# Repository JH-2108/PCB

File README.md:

# Small devboard 

A custom RP2040-based development board designed from scratch in KiCAD as part of Hack Club Half Life. 

The DevBoard is a compact general-purpose development platform with native USB-C connectivity, external QSPI flash, 3.3V power regulation, GPIO breakout, onboard controls, and a status LED. The board is intended to be used for embedded programming, electronics experimentation, robotics, sensors, displays, and future hardware projects. 

# Features 
- Raspberry Pi RP2040 microcontroller
- Native USB-C connectivity
- External QSPI flash
- 12 MHz crystal oscillator
- 3.3V power regulation
- 2x20 GPIO breakout pins
- BOOTSEL and RESET buttons
- Onboard status LED
- SMD components
- Custom PCB designed in KiCAD

# Hardware 
The board is built around the RP2040 and follows the required circuity for its power, clock, USB, and external flash interfaces. 

# Main components
- RP2040 MCU
- W25Q128 QSPI flash
- 12 MHz crystal
- USB-C connector
- 3.3V LDO regulator
- Decoupling and filtering capacitors
- USB-C CC resistors
- GPIO headers
- RESET and BOOTSEL buttons
- Status LED

# Firmware
The devboard will be programmed using the Raspberry Pi Pico SDK and C/C++. 

The initial firmware will provide: 
- RP2040 boot and initialization
- USB connectivity
- GPIO testing
- Status LED control
- Board diagnostics
- USB serial communication

A diagnostic firmware can be used to verify that the assembled PCB is functioning correctly. 

# PC software
A small optional Python utility may be developed to communicated with the board over USB serial. 

This can be used to 
- Display board information
- Run hardware tests
- Control the onboard LED
- Test GPIO
- Monitor diagnostic output

# Design
The PCB and schematic are designed using KiCAD. 
Project files include: 
- Schematic
- PCB layout
- Component/footprint assignments
- BOM
- Manufacturing files

# Design process
1. select and verify components for pricing and whether it is within budget range
2. create the schematic
3. assign symbols and footprints
4. design the PCB layout
5. route the board
6. run electrical and design rule checks
7. generate gerber files
8. assemble the PCB
9. develop and test firmware
10. test the complete board

# Project goals
The main goal is to design and build a fully functioning custom development board rather than relying on an existing development board such as the Raspberry Pi Pico. 

The project combines: 
- PCB design
- embedded systems
- electronics
- Firmware development
- USB communication
- hardware testing
- software development

# project images

**Schematic** 

**PCB layout**

**3d Render**

**Finished PCB**
a photo will be added here

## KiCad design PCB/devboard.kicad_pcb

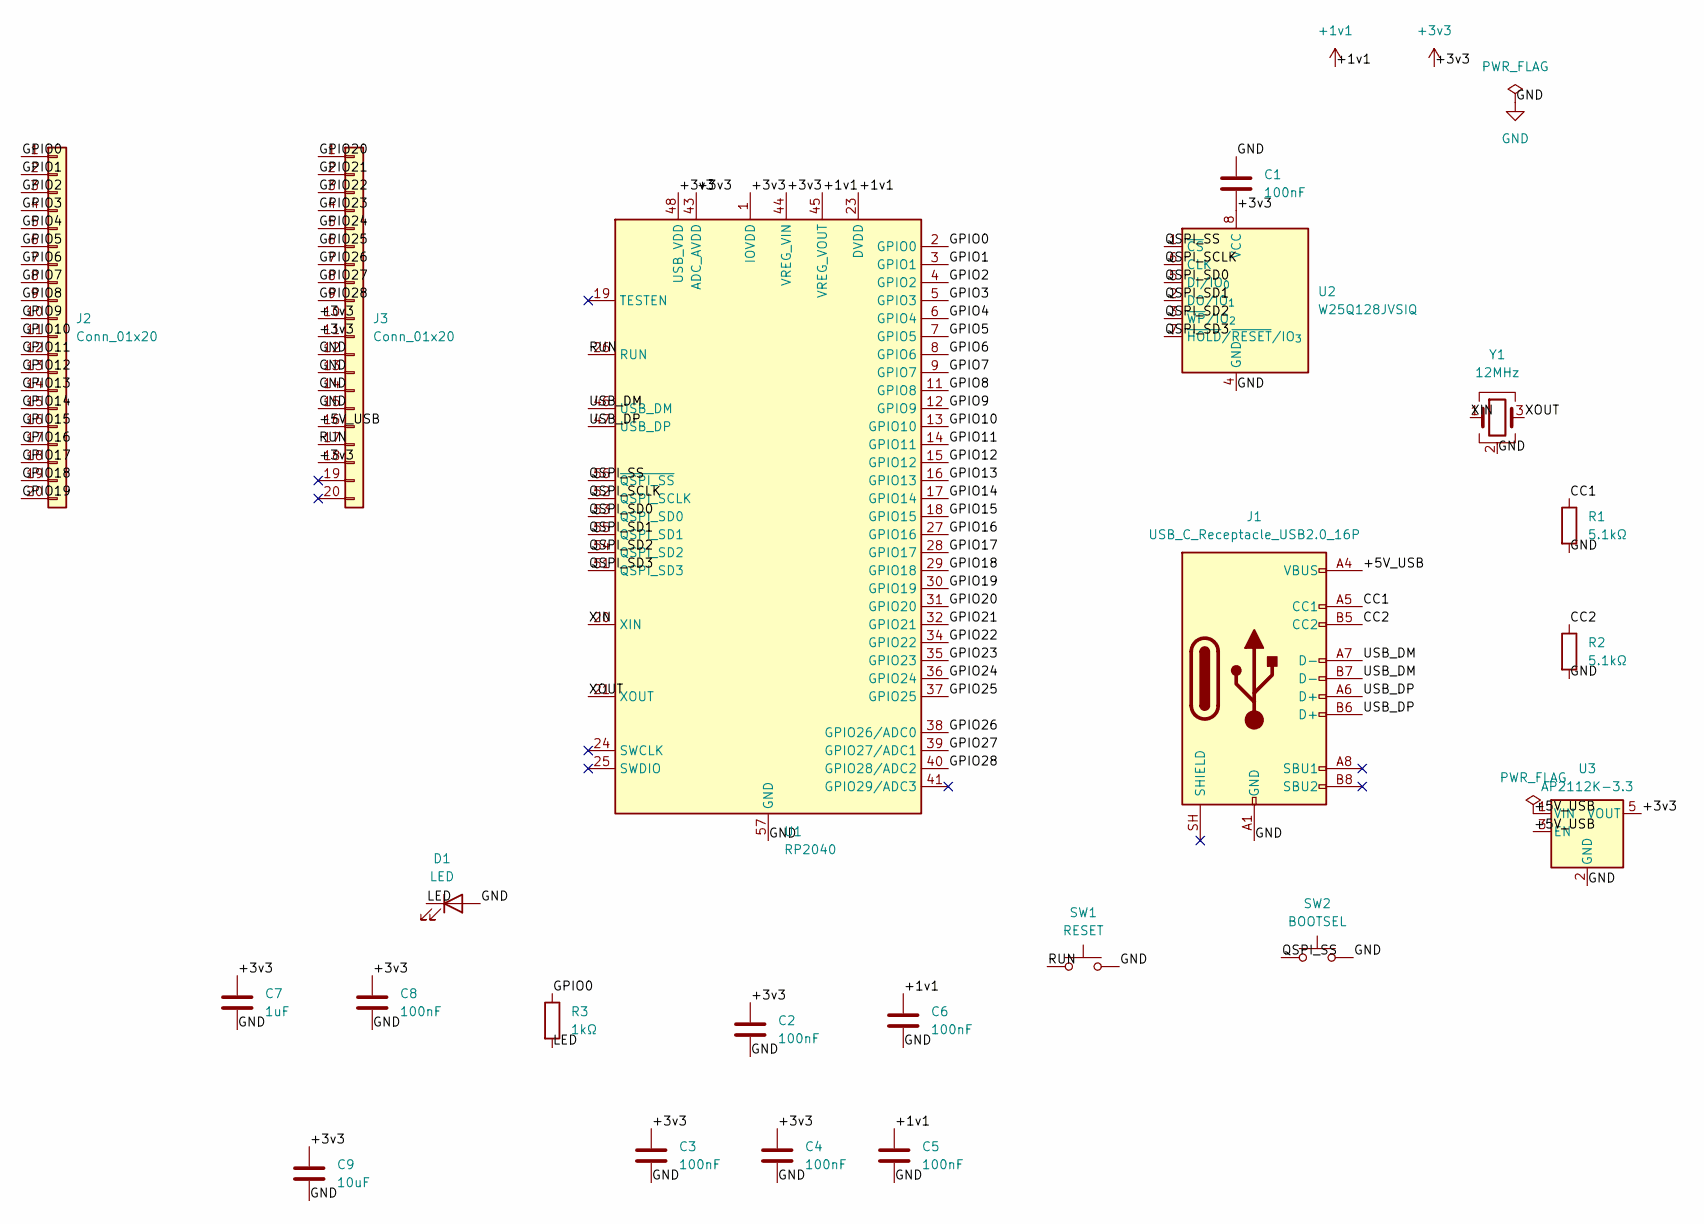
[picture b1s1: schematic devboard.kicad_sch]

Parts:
C1, C2, C3, C4, C5, C6, C8: 100nF; C_0603_1608Metric
C7: 1uF; C_0603_1608Metric
C9: 10uF; C_0603_1608Metric
D1: LED; LED_0603_1608Metric
J1: USB_C_Receptacle_USB2.0_16P; USB_C_Receptacle_GCT_USB4105-xx-A_16P_TopMnt_Horizontal
J2, J3: Conn_01x20; PinHeader_1x20_P2.54mm_Vertical
R1, R2: 5.1kΩ; R_0603_1608Metric
R3: 1kΩ; R_0603_1608Metric
SW1: RESET; SW_Push_1P1T_NO_E-Switch_TL3301NxxxxxG
SW2: BOOTSEL; SW_Push_1P1T_NO_E-Switch_TL3301NxxxxxG
U1: RP2040; QFN-56-1EP_7x7mm_P0.4mm_EP3.2x3.2mm
U2: W25Q128JVSIQ; SOIC-8_5.3x5.3mm_P1.27mm
U3: AP2112K-3.3; SOT-23-5
Y1: 12MHz; Crystal_SMD_3225-4Pin_3.2x2.5mm

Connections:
+1v1: C5.1, C6.1, U1.23 (DVDD), U1.45 (VREG_VOUT), U1.50 (DVDD)
+3v3: C1.2, C2.1, C3.1, C4.1, C7.1, C8.1, C9.1, J3.10, J3.11, J3.18, U1.1 (IOVDD), U1.10 (IOVDD), U1.22 (IOVDD), U1.33 (IOVDD), U1.42 (IOVDD), U1.43 (ADC_AVDD), U1.44 (VREG_VIN), U1.48 (USB_VDD), U1.49 (IOVDD), U2.8 (VCC), U3.5 (VOUT)
/+5V_USB: J1.A4 (VBUS), J1.A9 (VBUS), J1.B4 (VBUS), J1.B9 (VBUS), J3.16, U3.1 (VIN), U3.3 (EN)
/CC1: J1.A5 (CC1), R1.1
/CC2: J1.B5 (CC2), R2.1
/GPIO0: J2.1, R3.1, U1.2 (GPIO0)
/GPIO1: J2.2, U1.3 (GPIO1)
/GPIO2: J2.3, U1.4 (GPIO2)
/GPIO3: J2.4, U1.5 (GPIO3)
/GPIO4: J2.5, U1.6 (GPIO4)
/GPIO5: J2.6, U1.7 (GPIO5)
/GPIO6: J2.7, U1.8 (GPIO6)
/GPIO7: J2.8, U1.9 (GPIO7)
/GPIO8: J2.9, U1.11 (GPIO8)
/GPIO9: J2.10, U1.12 (GPIO9)
/GPIO10: J2.11, U1.13 (GPIO10)
/GPIO11: J2.12, U1.14 (GPIO11)
/GPIO12: J2.13, U1.15 (GPIO12)
/GPIO13: J2.14, U1.16 (GPIO13)
/GPIO14: J2.15, U1.17 (GPIO14)
/GPIO15: J2.16, U1.18 (GPIO15)
/GPIO16: J2.17, U1.27 (GPIO16)
/GPIO17: J2.18, U1.28 (GPIO17)
/GPIO18: J2.19, U1.29 (GPIO18)
/GPIO19: J2.20, U1.30 (GPIO19)
/GPIO20: J3.1, U1.31 (GPIO20)
/GPIO21: J3.2, U1.32 (GPIO21)
/GPIO22: J3.3, U1.34 (GPIO22)
/GPIO23: J3.4, U1.35 (GPIO23)
/GPIO24: J3.5, U1.36 (GPIO24)
/GPIO25: J3.6, U1.37 (GPIO25)
/GPIO26: J3.7, U1.38 (GPIO26/ADC0)
/GPIO27: J3.8, U1.39 (GPIO27/ADC1)
/GPIO28: J3.9, U1.40 (GPIO28/ADC2)
/LED: D1.1 (K), R3.2
/QSPI_SCLK: U1.52 (QSPI_SCLK), U2.6 (CLK)
/QSPI_SD0: U1.53 (QSPI_SD0), U2.5 (DI/IO_{0})
/QSPI_SD1: U1.55 (QSPI_SD1), U2.2 (DO/IO_{1})
/QSPI_SD2: U1.54 (QSPI_SD2), U2.3 (~WP/IO_{2})
/QSPI_SD3: U1.51 (QSPI_SD3), U2.7 (~HOLD/~RESET/IO_{3})
/QSPI_SS: SW2.1, U1.56 (~QSPI_SS), U2.1 (~CS)
/RUN: J3.17, SW1.1, U1.26 (RUN)
/USB_DM: J1.A7 (D-), J1.B7 (D-), U1.46 (USB_DM)
/USB_DP: J1.A6 (D+), J1.B6 (D+), U1.47 (USB_DP)
/XIN: U1.20 (XIN), Y1.1
/XOUT: U1.21 (XOUT), Y1.3
GND: C1.1, C2.2, C3.2, C4.2, C5.2, C6.2, C7.2, C8.2, C9.2, D1.2 (A), J1.A1 (GND), J1.A12 (GND), J1.B1 (GND), J1.B12 (GND), J3.12, J3.13, J3.14, J3.15, R1.2, R2.2, SW1.2, SW2.2, U1.57 (GND), U2.4 (GND), U3.2 (GND), Y1.2 (G), Y1.4 (G)

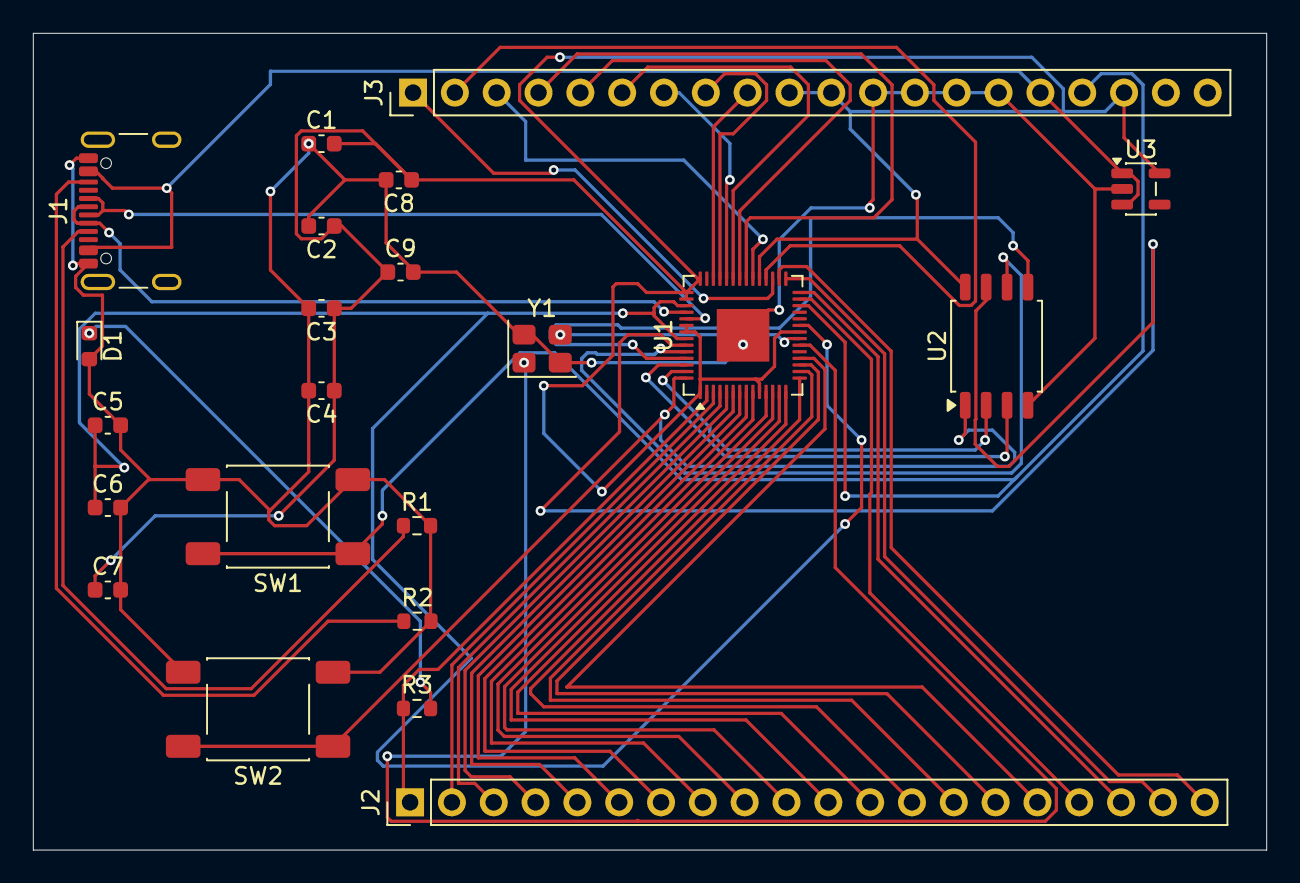
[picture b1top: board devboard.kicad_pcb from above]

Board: 2 copper layers, 74.9 x 49.6 mm, 22 parts (0 on the bottom side), 47 nets.

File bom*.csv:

"Reference","Qty","Value","DNP","Exclude from BOM","Exclude from Board","Exclude from Simulation","Exclude from Position Files","Footprint","Datasheet"
"C1,C2,C3,C4,C5,C6,C8","7","100nF","","","","","${EXCLUDE_FROM_POS_FILES}","Capacitor_SMD:C_0603_1608Metric",""
"C7","1","1uF","","","","","${EXCLUDE_FROM_POS_FILES}","Capacitor_SMD:C_0603_1608Metric",""
"C9","1","10uF","","","","","${EXCLUDE_FROM_POS_FILES}","Capacitor_SMD:C_0603_1608Metric",""
"D1","1","LED","","","","","${EXCLUDE_FROM_POS_FILES}","LED_SMD:LED_0603_1608Metric",""
"J1","1","USB_C_Receptacle_USB2.0_16P","","","","","${EXCLUDE_FROM_POS_FILES}","Connector_USB:USB_C_Receptacle_GCT_USB4105-xx-A_16P_TopMnt_Horizontal","https://www.usb.org/sites/default/files/documents/usb_type-c.zip"
"J2,J3","2","Conn_01x20","","","","","${EXCLUDE_FROM_POS_FILES}","Connector_PinHeader_2.54mm:PinHeader_1x20_P2.54mm_Vertical",""
"R1,R2","2","5.1kΩ","","","","","${EXCLUDE_FROM_POS_FILES}","Resistor_SMD:R_0603_1608Metric",""
"R3","1","1kΩ","","","","","${EXCLUDE_FROM_POS_FILES}","Resistor_SMD:R_0603_1608Metric",""
"SW1","1","RESET","","","","","${EXCLUDE_FROM_POS_FILES}","Button_Switch_SMD:SW_Push_1P1T_NO_E-Switch_TL3301NxxxxxG",""
"SW2","1","BOOTSEL","","","","","${EXCLUDE_FROM_POS_FILES}","Button_Switch_SMD:SW_Push_1P1T_NO_E-Switch_TL3301NxxxxxG",""
"U1","1","RP2040","","","","","${EXCLUDE_FROM_POS_FILES}","Package_DFN_QFN:QFN-56-1EP_7x7mm_P0.4mm_EP3.2x3.2mm","https://datasheets.raspberrypi.com/rp2040/rp2040-datasheet.pdf"
"U2","1","W25Q128JVSIQ","","","","","${EXCLUDE_FROM_POS_FILES}","Package_SO:SOIC-8_5.3x5.3mm_P1.27mm","https://www.winbond.com/resource-files/w25q128jv_dtr%20revc%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"
"U3","1","AP2112K-3.3","","","","","${EXCLUDE_FROM_POS_FILES}","Package_TO_SOT_SMD:SOT-23-5","https://www.diodes.com/assets/Datasheets/AP2112.pdf"
"Y1","1","12MHz","","","","","${EXCLUDE_FROM_POS_FILES}","Crystal:Crystal_SMD_3225-4Pin_3.2x2.5mm",""
